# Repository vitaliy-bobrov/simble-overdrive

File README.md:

# Simble Overdrive

Simble an overdrive baced on Mad Professor Simble schematic traced by folks at [FreeStompBoxes.org](https://www.freestompboxes.org/viewtopic.php?f=7&t=24553&start=60).

The repository contains KiCad source files: schematic, PCB, BOM.

## Schematic

## PCB (3D preview)

## Interactive BOM

👉 [BOM](https://vitaliy-bobrov.github.io/simble-overdrive/)

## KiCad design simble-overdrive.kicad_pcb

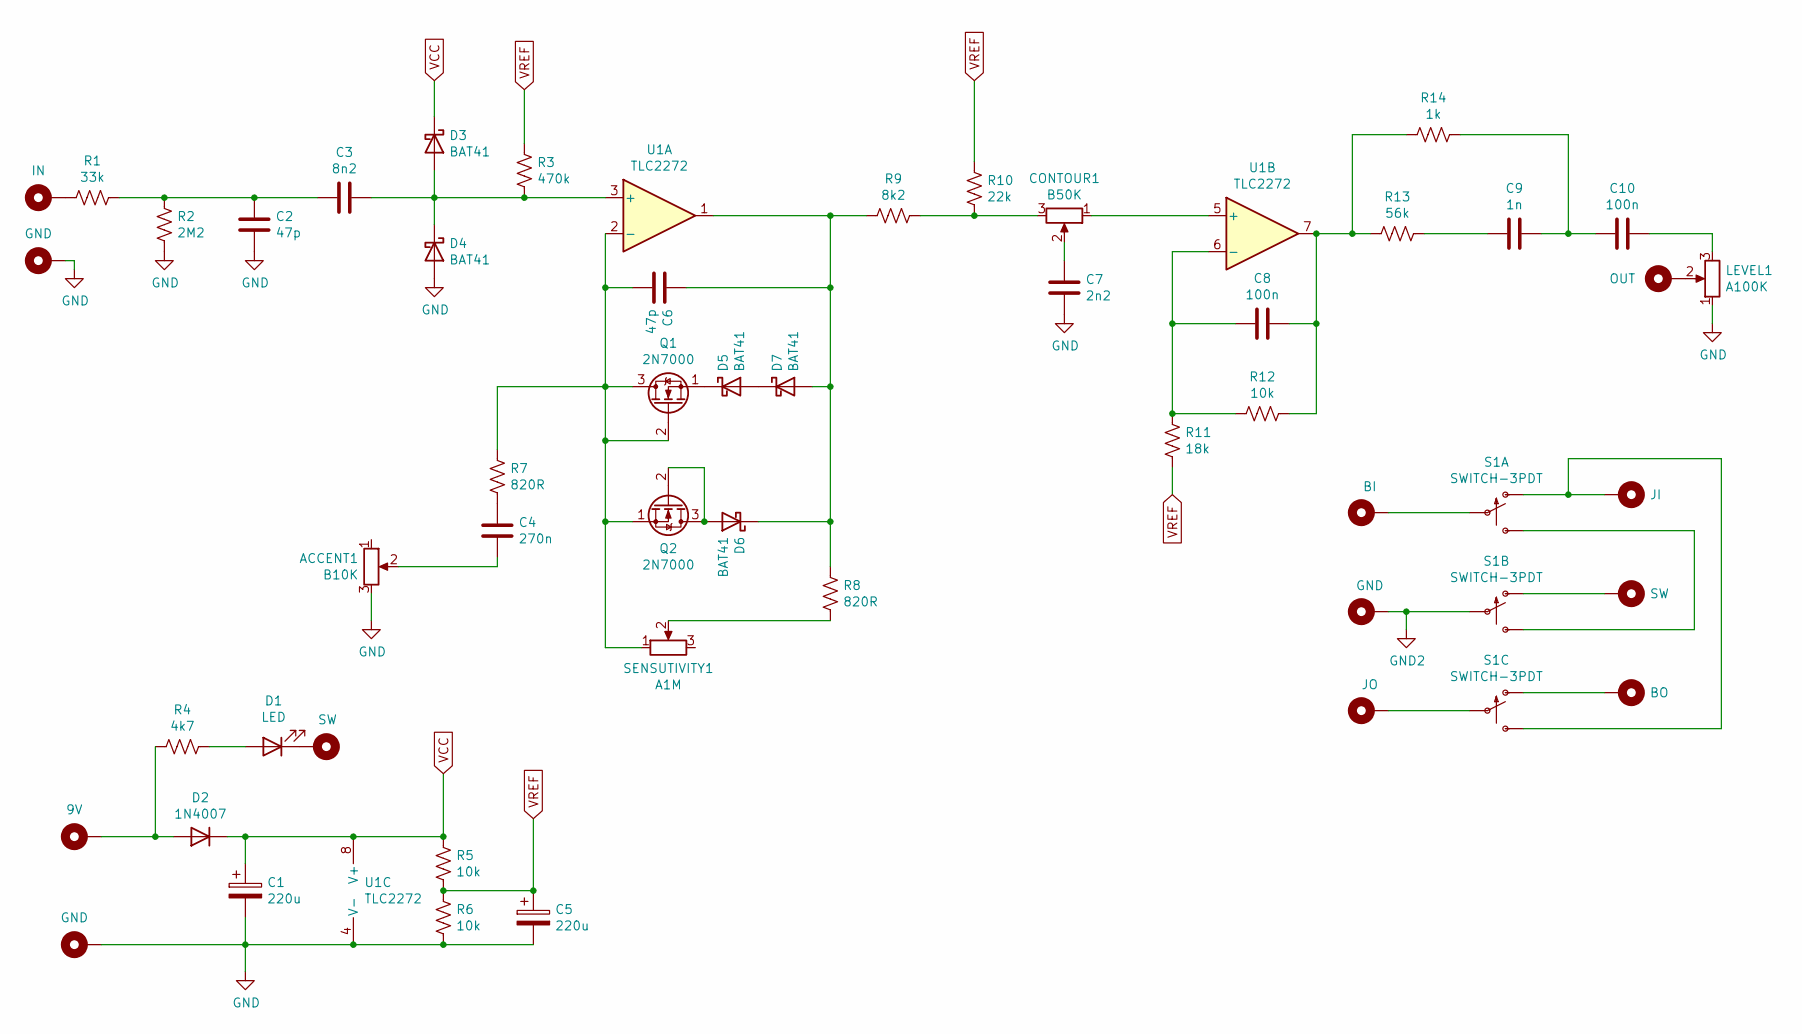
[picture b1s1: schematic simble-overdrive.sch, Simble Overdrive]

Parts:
ACCENT1: B10K; 16MM_B.MOUNT
C1, C5: 220u; 0502
C2, C6: 47p; C_Disc_D6.0mm_W2.5mm_P5.00mm
C3: 8n2; C_Disc_D6.0mm_W2.5mm_P5.00mm
C4: 270n; C_Disc_D6.0mm_W2.5mm_P5.00mm
C7: 2n2; C_Disc_D6.0mm_W2.5mm_P5.00mm
C8, C10: 100n; C_Disc_D6.0mm_W2.5mm_P5.00mm
C9: 1n; C_Disc_D6.0mm_W2.5mm_P5.00mm
CONTOUR1: B50K; 16MM_B.MOUNT
D1: LED; LED_D5.0mm
D2: 1N4007; D_DO-41_SOD81_P10.16mm_Horizontal
D3, D4, D5, D6, D7: BAT41; D_DO-35_SOD27_P7.62mm_Horizontal
H1: IN; PAD1
H2: 9V; PAD1
H3, H6, H8: GND; PAD1
H4, H11: SW; PAD1
H5: OUT; PAD1
H7: BI; PAD1
H9: JO; PAD1
H10: JI; PAD1
H12: BO; PAD1
LEVEL1: A100K; 16MM_B.MOUNT
Q1, Q2: 2N7000; TO92
R1: 33k; 0.3%22.B
R2: 2M2; 0.3%22.B
R3: 470k; 0.3%22.B
R4: 4k7; 0.3%22.B
R5, R6, R12: 10k; 0.3%22.B
R7, R8: 820R; 0.3%22.B
R9: 8k2; 0.3%22.B
R10: 22k; 0.3%22.B
R11: 18k; 0.3%22.B
R13: 56k; 0.3%22.B
R14: 1k; 0.3%22.B
S1: SWITCH-3PDT; 3PDT.LUGS.SPF
SENSUTIVITY1: A1M; 16MM_B.MOUNT
U1: TLC2272; DIP-8_W7.62mm_Socket

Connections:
GND: ACCENT1.3, C1.2, C2.2, C5.2, C7.2, D4.2 (A), H3.1, H6.1, LEVEL1.1, R2.2, R6.2, U1.4 (V-); also elsewhere on the board
GND2: H8.1, S1.P$5
unnamed 3: ACCENT1.2, C4.2; also elsewhere on the board
unnamed: C2.1, C3.2, R1.1, R2.1
unnamed: C3.1, D3.2 (A), D4.1 (K), R3.2, U1.3 (+)
unnamed: C4.1, R7.2
unnamed: C6.1, D6.1 (K), D7.2 (A), R8.1, R9.2, U1.1
unnamed 8: C6.2, Q1.2 (G), Q1.3 (D), Q2.1 (S), R7.1, SENSUTIVITY1.1, U1.2 (-); also elsewhere on the board
unnamed 9: C7.1, CONTOUR1.2; also elsewhere on the board
unnamed: C8.1, R12.1, R13.2, R14.2, U1.7
unnamed: C8.2, R11.1, R12.2, U1.6 (-)
unnamed: C9.2, R13.1
unnamed 13: C10.1, LEVEL1.3; also elsewhere on the board
unnamed: C9.1, C10.2, R14.1
unnamed 15: CONTOUR1.1, U1.5 (+); also elsewhere on the board
unnamed 16: CONTOUR1.3, R9.1, R10.2; also elsewhere on the board
unnamed: D1.1 (K), H4.1
unnamed: D1.2 (A), R4.2
unnamed: D2.2 (A), H2.1, R4.1
unnamed: D5.1 (K), Q1.1 (S)
unnamed: D5.2 (A), D7.1 (K)
unnamed: D6.2 (A), Q2.2 (G), Q2.3 (D)
unnamed: H1.1, R1.2
unnamed 24: H5.1, LEVEL1.2; also elsewhere on the board
unnamed: H7.1, S1.P$2
unnamed: H9.1, S1.P$8
unnamed: H10.1, S1.P$1 (O), S1.P$9 (S)
unnamed: H11.1, S1.P$4 (O)
unnamed: H12.1, S1.P$7 (O)
unnamed 30: R8.2, SENSUTIVITY1.2; also elsewhere on the board
unnamed: S1.P$3 (S), S1.P$6 (S)
VCC: C1.1, D2.1 (K), D3.1 (K), R5.1, U1.8 (V+)
VREF: C5.1, R3.1, R5.2, R6.1, R10.1, R11.2

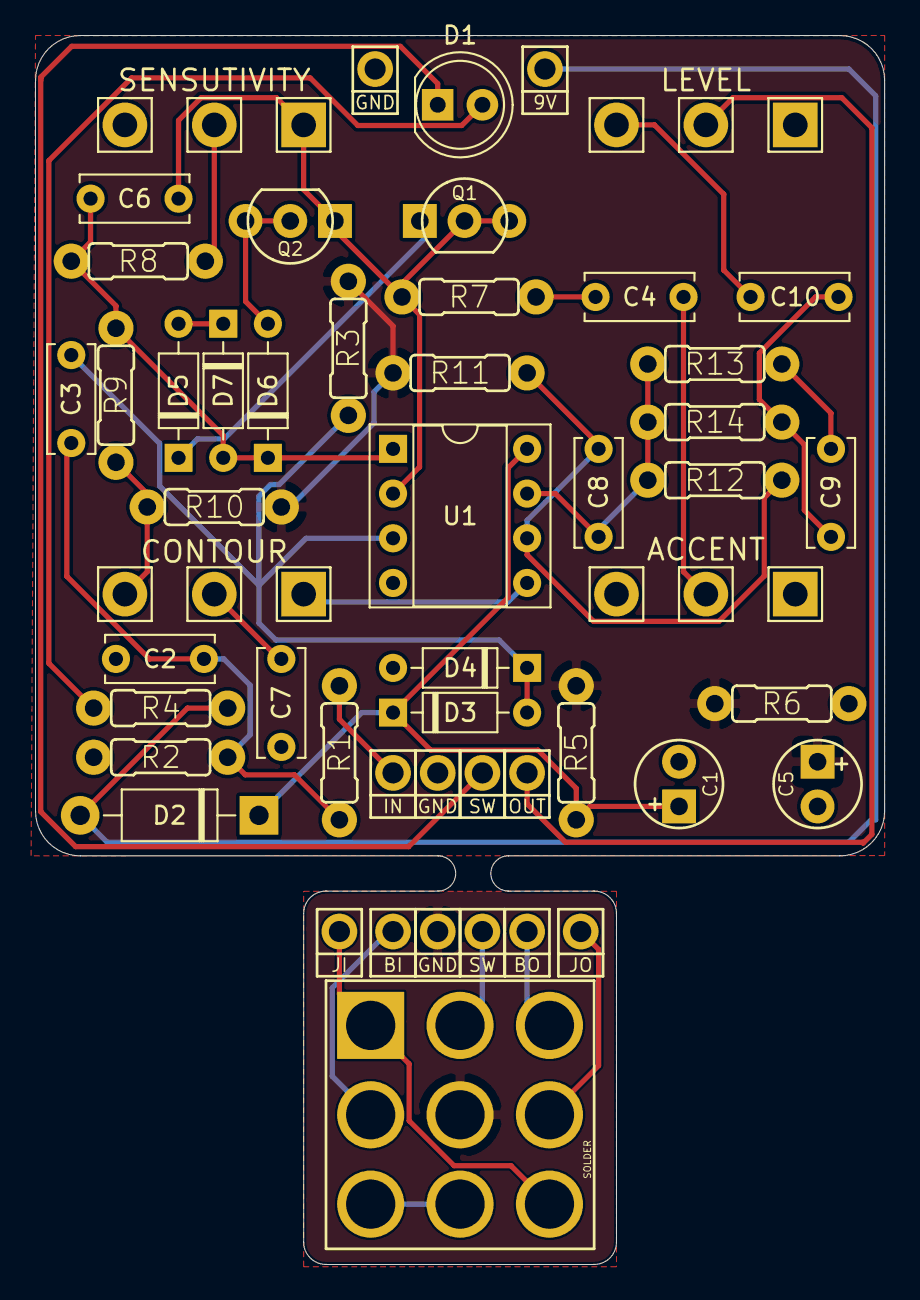
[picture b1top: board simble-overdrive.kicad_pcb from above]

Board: 2 copper layers, 48.3 x 69.9 mm, 51 parts (0 on the bottom side), 33 nets.

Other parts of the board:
ACCENT: B10K; 16MM_B.MOUNT
CONTOUR: B50K; 16MM_B.MOUNT
LEVEL: A100K; 16MM_B.MOUNT
SENSUTIVITY: A1M; 16MM_B.MOUNT

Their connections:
GND: ACCENT.3, LEVEL.1; also elsewhere on the board
unnamed 3: ACCENT.2; also elsewhere on the board
unnamed 8: SENSUTIVITY.1; also elsewhere on the board
unnamed 9: CONTOUR.2; also elsewhere on the board
unnamed 13: LEVEL.3; also elsewhere on the board
unnamed 15: CONTOUR.1; also elsewhere on the board
unnamed 16: CONTOUR.3; also elsewhere on the board
unnamed 24: LEVEL.2; also elsewhere on the board
unnamed 30: SENSUTIVITY.2; also elsewhere on the board

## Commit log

2020-09-27 v1.1
2020-09-27 update images path
2020-10-04 minor fixes
